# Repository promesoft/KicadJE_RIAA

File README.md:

# KicadJE_RIAA
RIAA apllifier test

# Status - RIAA installed in stereo setup
## Initial 
| Stage  | Detail | Status |
| ------------- | ------------- | ------------- |
| create material  | sch/pcb | OK  |
| | gerber | OK |
| production  |   | OK |
|  | produced | OK |
|  | delivered | OK |
## Preliminary validation
| Test  | Detail | Status |
| ------------- | ------------- | ------------- |
| Initial Inspection | | Chose different RCA |
| Initial Technical Test |  | Different RCA does not match pins |
| Initial Product Test |  | Working - no hum |

## Secondary validation
| Test  | Detail | Status |
| ------------- | ------------- |------------- |
| Product Test |  | |
| Product Test |  |  |
| Quality | | |
| Quality | | |
| Long Term Product Test |  |  |
| Power Draw |  | 

## Errata
### Errata -
1 - RCA footprint wrong (flip gnd and right)

2 - V-GND 2 does not have resistor balance - only LED indicator as input

3 - C107, C109, C111, C112 should either not be mounted or significantly smaller (10nF ?)

4 - U302B needs an 18k to GND on pin 5

## Issues and Notes
### 

# Pictures

# Inspiration

http://audio.engineeringvista.com/AudioKits/Phono-1/Design/Part6.htm

http://sound.whsites.net/project25.htm

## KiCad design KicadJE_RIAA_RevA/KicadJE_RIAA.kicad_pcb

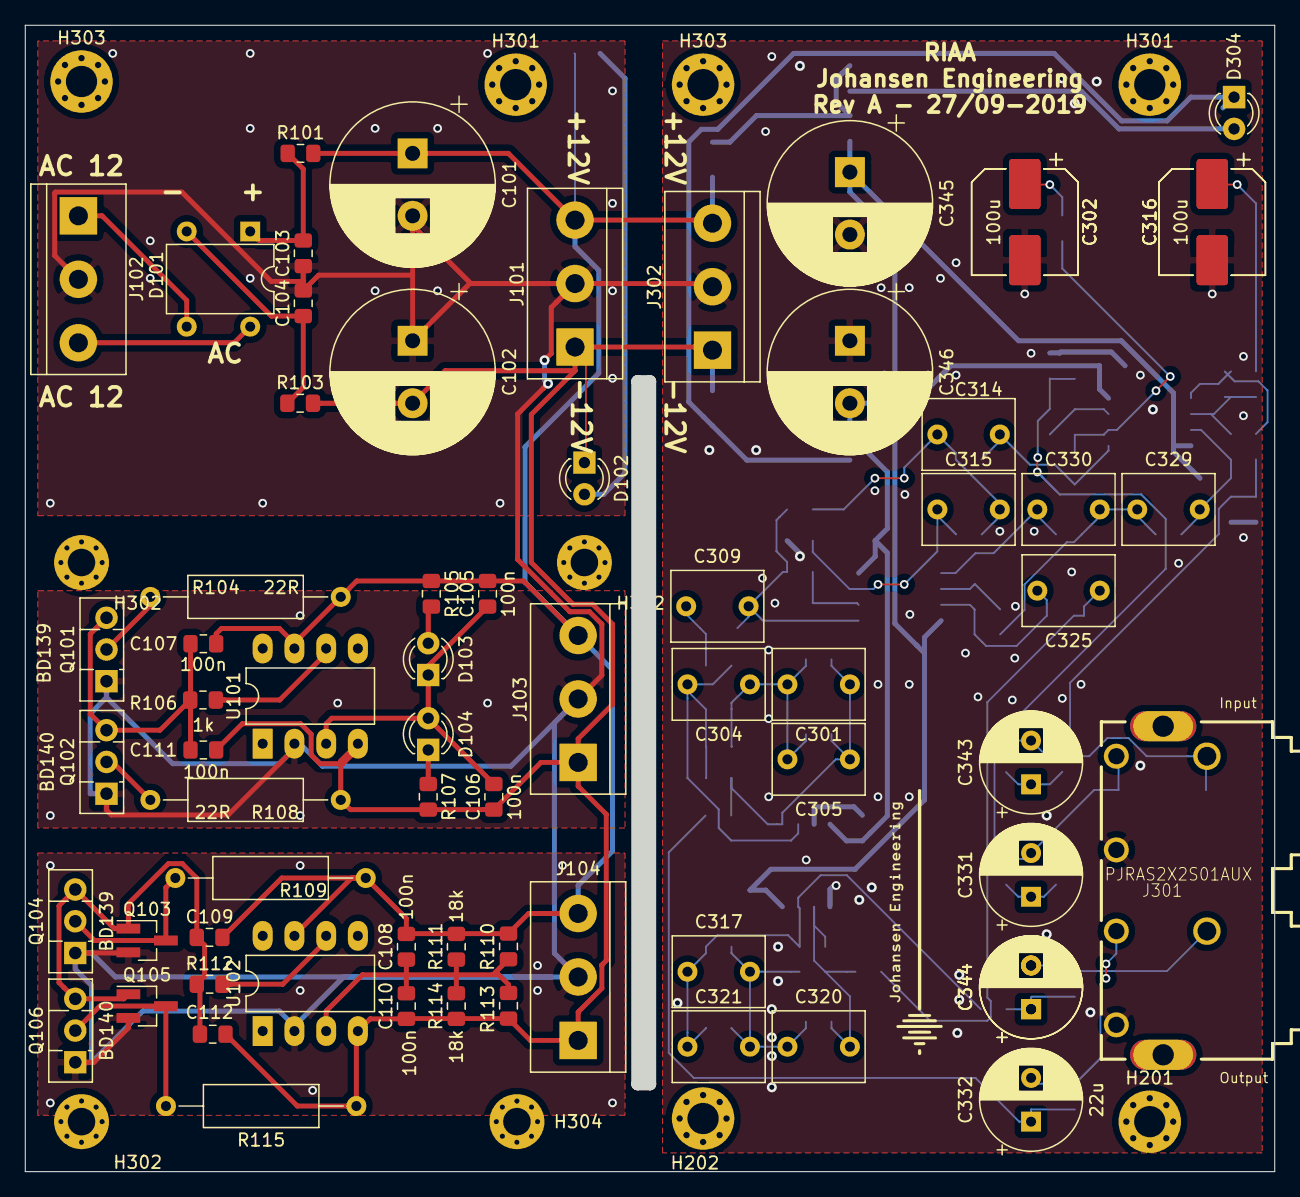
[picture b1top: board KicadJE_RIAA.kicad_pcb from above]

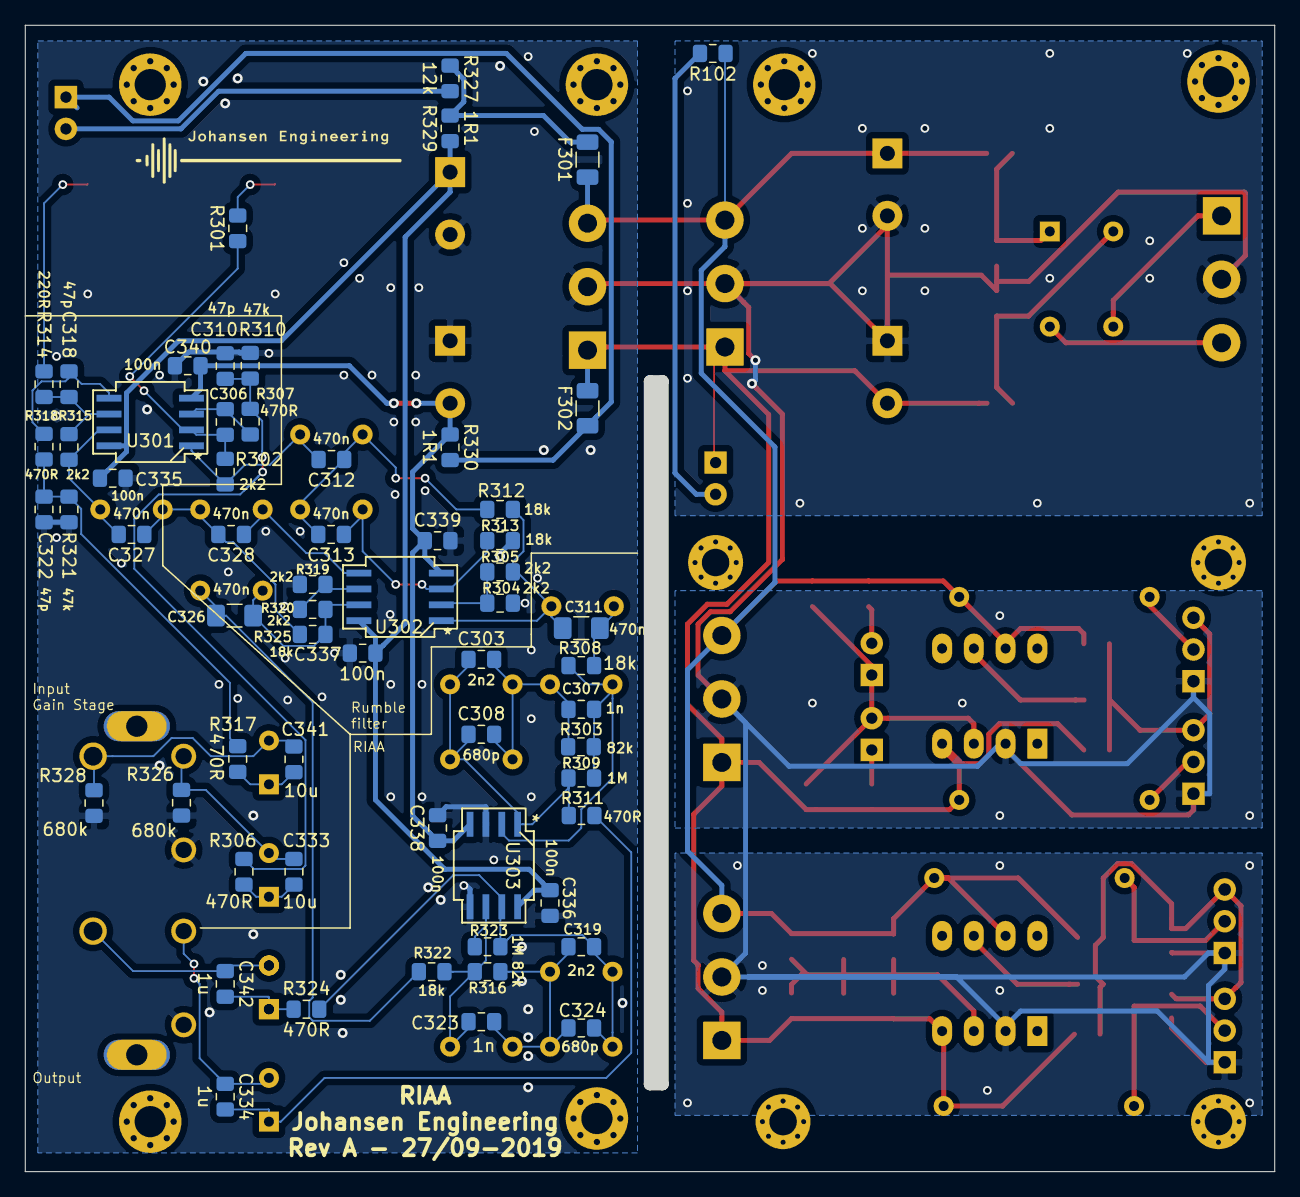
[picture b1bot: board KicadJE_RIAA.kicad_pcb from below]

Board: 2 copper layers, 100.0 x 91.8 mm, 140 parts (62 on the bottom side), 59 nets.

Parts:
C101, C102, C345, C346: 470u; CP_Radial_D13.0mm_P5.00mm
C103, C104, C105, C106, C107, C108, C109, C110, C111, C112, C335, C336, C337, C338, C339, C340: 100n; C_0805_2012Metric_Pad1.15x1.40mm_HandSolder
C301, C317: 2n2_THT; C_Rect_L7.2mm_W5.5mm_P5.00mm_FKS2_FKP2_MKS2_MKP2
C302, C302#2, C316, C316#2: 100u; CP_Elec_8x6.5
C303, C319: 2n2; C_0805_2012Metric_Pad1.15x1.40mm_HandSolder
C304, C320: 1n_THT; C_Rect_L7.2mm_W5.5mm_P5.00mm_FKS2_FKP2_MKS2_MKP2
C305, C321: 680p_THT; C_Rect_L7.2mm_W5.5mm_P5.00mm_FKS2_FKP2_MKS2_MKP2
C306, C310, C318, C322: 47p; C_0805_2012Metric_Pad1.15x1.40mm_HandSolder
C307, C323: 1n; C_0805_2012Metric_Pad1.15x1.40mm_HandSolder
C308, C324: 680p; C_0805_2012Metric_Pad1.15x1.40mm_HandSolder
C309, C314, C315, C325, C329, C330: 470n_THT; C_Rect_L7.2mm_W5.5mm_P5.00mm_FKS2_FKP2_MKS2_MKP2
C311, C326: 470n; C_1206_3216Metric_Pad1.42x1.75mm_HandSolder
C312, C313, C327, C328: 470n; C_0805_2012Metric_Pad1.15x1.40mm_HandSolder
C331, C343: 10u; CP_Radial_D8.0mm_P3.50mm
C332, C344, C344#2: 22u; CP_Radial_D8.0mm_P3.50mm
C333, C341: 10u; C_0805_2012Metric_Pad1.15x1.40mm_HandSolder
C334, C342: 1u; C_0805_2012Metric_Pad1.15x1.40mm_HandSolder
D101: DF08M; Diode_Bridge_DIP-4_W7.62mm_P5.08mm
D102, D103, D104, D304: LED; LED_D3.0mm
F301, F302: Polyfuse; Fuse_1206_3216Metric
H201, H202, H301, H301#2, H303, H303#2: 2,5mm; MountingHole_2.5mm_Pad_Via
H302, H302#2, H302#3, H304: 2,2mm; MountingHole_2.2mm_M2_Pad_Via
J101, J102, J103, J104, J302: Conn_01x03; TerminalBlock_bornier-3_P5.08mm
J301: PJRAS2X2S01AUX; PJRAS2X2S01AUX_RCA
Q101, Q104: BD139; TO-126-3_Vertical
Q102, Q106: BD140; TO-126-3_Vertical
Q103: MMBT2222A; SOT-23_Handsoldering
Q105: MMBT2907A; SOT-23_Handsoldering
R101, R103, R329, R330: 1R1; R_0805_2012Metric_Pad1.15x1.40mm_HandSolder
R102, R327: 12k; R_0805_2012Metric_Pad1.15x1.40mm_HandSolder
R104, R108, R109, R115: 22R; R_Axial_DIN0309_L9.0mm_D3.2mm_P15.24mm_Horizontal
R105, R107: 10k; R_0805_2012Metric_Pad1.15x1.40mm_HandSolder
R106, R112: 1k; R_0805_2012Metric_Pad1.15x1.40mm_HandSolder
R110, R113: 22k; R_0805_2012Metric_Pad1.15x1.40mm_HandSolder
R111, R114, R308, R312, R313, R322, R325: 18k; R_0805_2012Metric_Pad1.15x1.40mm_HandSolder
R301, R314: 220R; R_0805_2012Metric_Pad1.15x1.40mm_HandSolder
R302, R304, R305, R315, R319, R320: 2k2; R_0805_2012Metric_Pad1.15x1.40mm_HandSolder
R303, R316: 82k; R_0805_2012Metric_Pad1.15x1.40mm_HandSolder
R306, R307, R311, R317, R318, R324: 470R; R_0805_2012Metric_Pad1.15x1.40mm_HandSolder
R309, R323: 1M; R_0805_2012Metric_Pad1.15x1.40mm_HandSolder
R310, R321: 47k; R_0805_2012Metric_Pad1.15x1.40mm_HandSolder
R326, R328: 680k; R_0805_2012Metric_Pad1.15x1.40mm_HandSolder
U101, U102: TL071; DIP-8_W7.62mm_LongPads
U301, U302, U303: TL072; AJ_SO-8_5.3x6.2mm_P1.27mm

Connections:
+12V: C335.2, C336.2, C337.2, C345.1, R329.1, U301.8, U302.8, U303.8
-12V: C338.1, C339.1, C340.1, C346.2, R330.1, U301.4, U302.4, U303.4
/+PSU: C101.1, C105.2, C107.2, C108.2, C109.2, J101.3, J103.3, J104.3, J302.3, R101.2, R102.1, R104.1, R105.1, R109.1, R110.1, R111.2, U101.7, U102.7
/-PSU: C102.2, C106.1, C110.1, C111.1, C112.1, D102.1, J101.1, J103.1, J104.1, J302.1, R103.2, R107.2, R108.1, R113.2, R114.1, R115.1, U101.4, U102.4
/AC1: D101.3, J102.1
/AC3: D101.4, J102.3
/BR+: C103.2, D101.1, R101.1
/BR-: C104.1, D101.2, R103.1
GND: C101.2, C102.1, C103.1, C104.2, C302.2, C302#2.2, C310.2, C316.2, C316#2.2, C322.2, C335.1, C336.1, C337.1, C338.2, C339.2, C340.2, C345.2, C346.1, J101.2, J102.2, J103.2, J104.2, J301.1T1, J301.2T1, J302.2, Q101.1, Q102.1, Q103.2, Q104.1, Q105.2, Q106.1, R304.2, R310.1, R313.1, R319.2, R321.1, R326.2, R328.1, U101.2, U102.2, U303.3, U303.5
In_L: C331.1, C333.2, R306.2
In_R: C341.2, C343.1, R317.2
L_GainOut: C312.2, C314.2, R302.1, U301.1
L_Rumble_Out: C309.2, C311.2, R305.1, R312.1, U302.1
unnamed: C105.1, C106.2, D103.1, D104.2, U101.3
unnamed: C107.1, C111.2, Q101.3, Q102.3, R106.1
unnamed: C108.1, C110.2, R110.2, R111.1, R113.1, R114.2, U102.3
unnamed: C109.1, C112.2, Q103.1, Q104.3, Q105.1, Q106.3, R112.1
unnamed: C301.1, C303.1, C305.1, C308.1, R309.1, R311.2, U303.1
unnamed: C301.2, C303.2, C304.1, C305.2, C307.1, C308.2, R303.1
unnamed: C302.1, C302#2.1, R301.2
unnamed: C304.2, C307.2, R303.2, R308.1, R309.2, U303.2
unnamed: C306.1, R301.1, R302.2, U301.2
unnamed: C306.2, R307.1, U301.3
unnamed: C309.1, C311.1, R308.2
unnamed: C310.1, R306.1, R307.2, R310.2
unnamed: C312.1, C313.2, C314.1, C315.2, R312.2
unnamed: C313.1, C315.1, R313.2, U302.3
unnamed: C316.1, C316#2.1, R314.2
unnamed: C317.1, C319.1, C321.1, C324.1, R323.1, R324.2, U303.7
unnamed: C317.2, C319.2, C320.1, C321.2, C323.1, C324.2, R316.1
unnamed: C318.1, R314.1, R315.2, U301.6
unnamed: C318.2, R318.1, U301.5
unnamed: C320.2, C323.2, R316.2, R322.1, R323.2, U303.6
unnamed: C322.1, R317.1, R318.2, R321.2
unnamed: C325.1, C326.1, R322.2
unnamed: C327.1, C328.2, C329.1, C330.2, R325.2
unnamed: C328.1, C330.1, U302.5
unnamed: C331.2, C333.1, J301.2T2, R326.1
unnamed: C332.2, C334.1, J301.1T2
unnamed: C341.1, C343.2, J301.2S, R328.2
unnamed: C342.1, C344.2, C344#2.2, J301.1S
unnamed: D102.2, R102.2
unnamed: D103.2, R105.2
unnamed: D104.1, R107.1
unnamed: D304.1, F302.1, R330.2
unnamed: D304.2, R327.2
unnamed: F301.2, R327.1, R329.2
unnamed: Q101.2, R104.2
unnamed: Q102.2, R108.2
unnamed: Q103.3, Q104.2, R109.2
unnamed: Q105.3, Q106.2, R115.2
unnamed: R106.2, U101.6
unnamed: R112.2, U102.6
unnamed: R304.1, R305.2, U302.2
unnamed: R319.1, R320.2, U302.6
Out_L: C332.1, C334.2, R311.1
Out_R: C342.2, C344.1, C344#2.1, R324.1
R_GainOut: C327.2, C329.2, R315.1, U301.7
R_Rumble_Out: C325.2, C326.2, R320.1, R325.1, U302.7

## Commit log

2019-10-02 Migrated from Ate0Ate
2019-10-03 SCH incl AC driver
2019-10-03 Dual VGND
2019-10-03 Footprints for BJT
2019-10-03 hopefully it works
2019-10-03 Gerber
2020-02-18 Picture updates and BOM
2020-02-20 Rev B initiated - errata 1-4
